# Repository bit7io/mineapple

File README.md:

# mineapple

A project to design an open source, modular mining system based around the ASICs reverse engineered by the [bitaxe](https://bitaxe.org/) project and [OSMU](https://www.opensourceminers.org/) community.

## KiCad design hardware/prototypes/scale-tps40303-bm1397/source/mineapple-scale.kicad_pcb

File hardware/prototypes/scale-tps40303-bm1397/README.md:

# Prototype BM1397 Scale
Known issues:
- M1 footprint incorrect
- R10 part number/footprint incorrect
- J1/J2 - TagConnect connector was used instead of SKEDD

Changes for V1.0:
- Fix known issues
- Move power monitoring to Core boards
- Remove 4V0 input
- Balance number of VPWR/PGND pins

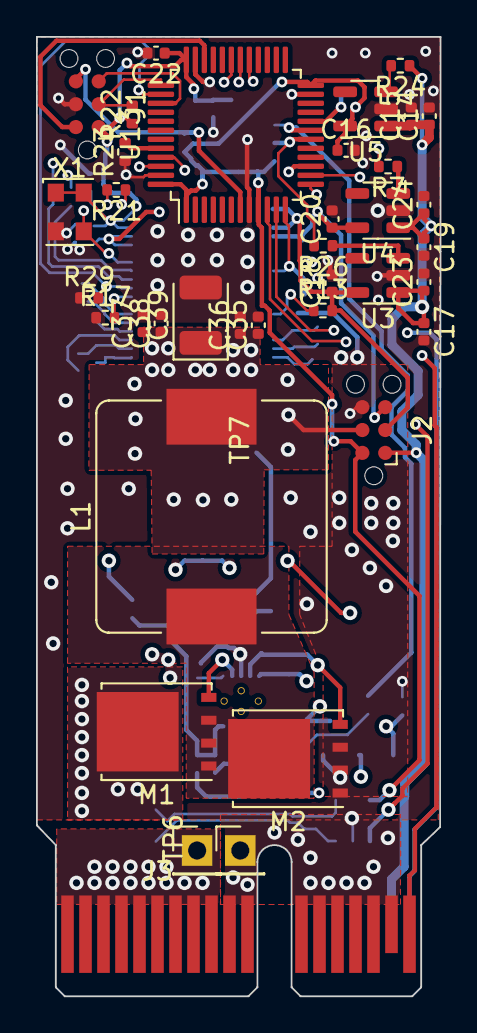
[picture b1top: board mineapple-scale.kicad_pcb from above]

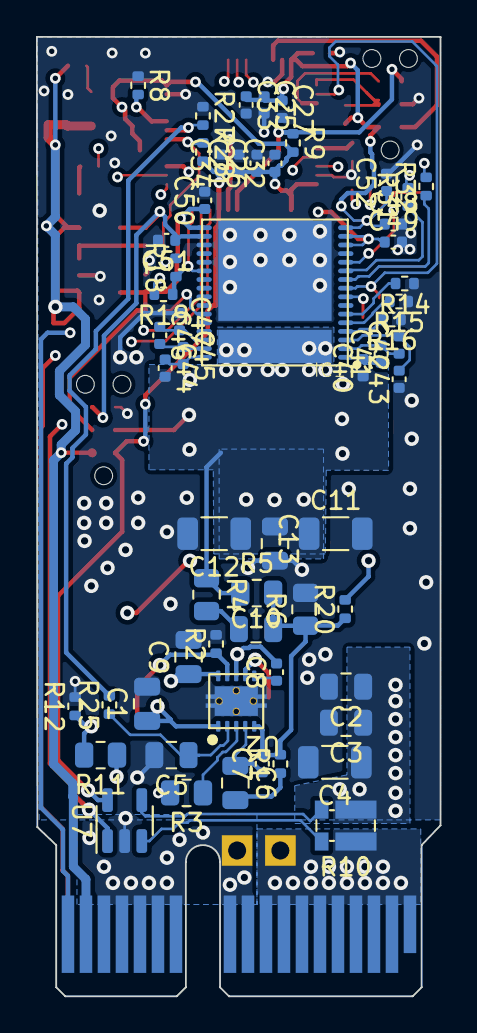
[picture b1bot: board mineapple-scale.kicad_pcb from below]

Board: 4 copper layers, 22.4 x 53.3 mm, 95 parts (58 on the bottom side), 58 nets.

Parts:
C1: 1uF; C_0805_2012Metric
C2, C3: 22uF; C_0805_2012Metric
C4: 47uF; C_1206_3216Metric
C5: 3.3nF; C_0805_2012Metric
C6: 11nF; C_0805_2012Metric
C7: 470pF; C_0402_1005Metric
C8, C22, C32, C33, C34: 100nF; C_0402_1005Metric
C9: 10uF; C_0805_2012Metric
C10: 3.9nF; C_0805_2012Metric
C11, C12: 220uF; C_1206_3216Metric
C13: 100uF; C_0805_2012Metric
C14, C16, C18, C20, C21, C23, C24, C27, C35, C37, C40, C41, C42, C43, C44, C45, C46, C47, C48, C49, C50, C51: 1uF; C_0402_1005Metric
C15, C17, C19, C36, C38, C52: 0.1uF; C_0402_1005Metric
C25: 10nF; C_0402_1005Metric
C26: 4.7uF; C_0402_1005Metric
C39: 330uF; CP_EIA-3528-21_Kemet-B
IC1: BM1397_mode1; BM1397
J1, J2: Conn_SKEDD_6pos; Tag-Connect_TC2030-IDC-NL_2x03_P1.27mm_Vertical
J3: MAS_Edge_Connector; BUS_PCIexpress_x1
L1: 1.3uH; L_Bourns_SRP1245A
M1: CSD17304Q3; TDSON-8-1
M2: CSD17573Q5B; TDSON-8-1
R1: 3.83k; R_0402_1005Metric
R2: 1.74k; R_0402_1005Metric
R3, R11: 100k; R_0805_2012Metric
R4: 432; R_0805_2012Metric
R5: 10k; R_0805_2012Metric
R6: 6.65k; R_0805_2012Metric
R7, R18, R20, R21, R25, R26, R31, R32: 1k; R_0402_1005Metric
R8, R9, R12, R13, R14, R15, R16, R17, R22, R23, R24, R27, R28, R29: 15k; R_0402_1005Metric
R10: 2mOhm; R_Shunt_Vishay_WSKW0612
R19: 2k; R_0402_1005Metric
TP6, TP7: TestPoint; PinHeader_1x01_P2.54mm_Vertical
U2: TPS40303DRCR; TPS40305
U3: MIC5504-1.8YM5; SOT-23-5
U4: TPS7A0508PDBV; SOT-23-5
U5: MIC5504-3.3YM5; SOT-23-5
U7: INA180A4; SOT-23-5
U13: STM32F072CBTx; LQFP-48_7x7mm_P0.5mm
X1: 25MHz; Oscillator_SMD_EuroQuartz_XO32-4Pin_3.2x2.5mm

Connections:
0V8: C20.1, C49.1, C51.1, IC1.14 (PLL_VDD), IC1.15 (VDDIO_08_0), IC1.18 (VDDIO_08_1), J2.5, U4.5 (OUT)
1V5: C11.1, C12.1, C13.1, C35.1, C36.1, C37.1, C38.1, C39.1, C40.1, C44.2, IC1.33 (VDD), J2.4, L1.2, R4.1, R5.1
1V8: C18.1, C22.1, C25.1, C27.1, C33.1, C48.1, C50.1, C52.1, IC1.16 (VDDIO_18_0), IC1.17 (VDDIO_18_1), J1.1, J2.3, R13.2, R22.1, U3.5 (VOUT), U13.36 (VDDIO2), X1.1 (EN), X1.4 (V+)
3V3: C16.1, C21.1, C26.1, C32.1, C34.1, J2.2, R9.2, R28.2, U5.5 (VOUT), U7.5 (V+), U13.1 (VBAT), U13.9 (VDDA), U13.24 (VDD), U13.48 (VDD)
4V0: C14.1, C15.1, C17.1, C19.1, C23.1, C24.1, J2.1, J3.A17 (4V0), R24.1, U3.1 (VIN), U4.1 (IN), U5.1 (VIN)
/MCU/SWDCLK: J1.3, R22.2, U13.37 (PA14)
/MCU/SWDIO: J1.2, U13.34 (PA13)
ADC12_IN0: U7.1, U13.10 (PA0)
ADC12_IN1: R11.2, R12.1, U13.11 (PA1)
CAN_RX: J3.A18 (CAN_RX), U13.45 (PB8)
CAN_TX: J3.B18 (CAN_TX), U13.46 (PB9)
EN0V8: R7.2, R8.2, U13.20 (PB2)
EN1V5: R25.2, R27.2, U13.19 (PB1)
EN1V8: R26.2, R28.1, U13.18 (PB0)
FB1V5: R20.2, U13.15 (PA5)
GND: C1.2, C2.2, C3.2, C4.2, C5.2, C9.2, C11.2, C12.2, C13.2, C14.2, C15.2, C16.2, C17.2, C18.2, C19.2, C20.2, C21.2, C22.2, C23.2, C24.2, C25.2, C26.2, C27.2, C32.2, C33.2, C34.2, C35.2, C36.2, C37.2, C38.2, C39.2, C43.1, C47.1, C48.2, C49.2, C50.2, C51.2, C52.2, IC1.13 (PLL_VSS), IC1.19 (VSS), IC1.21 (TEMP_N), IC1.34 (VSS_0), J1.4, J2.6, J3.A10 (PGND), J3.A11 (PGND), J3.A12 (PGND), J3.A13 (PGND), J3.A14 (PGND), J3.A15 (PGND), J3.A16 (PGND), J3.B10 (PGND), J3.B11 (PGND), J3.B12 (PGND), J3.B13 (PGND), J3.B14 (PGND), J3.B15 (PGND), J3.B16 (PGND), J3.B17 (PGND), M2.1 (S), M2.2 (S), M2.3 (S), R2.2, R6.2, R8.1, R12.2, R14.1, R15.1, R16.1, R17.1, R23.1, R27.1, R29.1, TP7.1, U2.11 (GND), U3.2 (GND), U4.2 (GND), U5.2 (GND), U7.2 (GND), U13.8 (VSSA), U13.23 (VSS), U13.35 (VSS), U13.47 (VSS), X1.2 (GND)
unnamed: C6.2, R1.1
unnamed: C10.1, R4.2
unnamed: IC1.4 (ADDR0), R16.2
unnamed: IC1.5 (ADDR1), R15.2
unnamed: IC1.6 (ADDR2), R14.2
unnamed: IC1.8 (BI), R17.2
unnamed: IC1.12 (CLKI), R21.2, X1.3 (OUT)
unnamed: IC1.27 (RI), R13.1
unnamed: C42.2, C43.2, IC1.3 (VDD1_0)
unnamed: C46.1, C47.2, IC1.30 (VDD1_1)
unnamed: C41.2, C42.1, IC1.2 (VDD2_0)
unnamed: C45.1, C46.2, IC1.31 (VDD2_1)
unnamed: C40.2, C41.1, IC1.1 (VDD3_0)
unnamed: C44.1, C45.2, IC1.32 (VDD3_1)
unnamed: C1.1, C2.1, C3.1, C4.1, M1.5 (D), R10.4, U2.1 (VDD)
unnamed: M1.4 (G), U2.7 (HDRV)
unnamed: C8.2, L1.1, M1.1 (S), M1.2 (S), M1.3 (S), M2.5 (D), U2.8 (SW)
unnamed: M2.4 (G), R2.1, U2.9 (LDRV/OC)
unnamed: C8.1, U2.6 (BOOT)
unnamed: C9.1, R3.2, U2.10 (BP)
unnamed: C6.1, C7.1, U2.4 (COMP)
unnamed: C5.1, R25.1, U2.2 (EN/SS)
unnamed: C7.2, C10.2, R1.2, R5.2, R6.1, R20.1, U2.5 (FB)
unnamed: R3.1, U2.3 (PGOOD)
unnamed: R26.1, U3.3 (EN)
unnamed: R7.1, U4.3 (EN)
unnamed: R24.2, U5.3 (EN)
unnamed: R10.2, U7.3 (+)
unnamed: R10.3, U7.4 (-)
unnamed: R23.2, U13.44 (BOOT0)
unnamed: R18.2, U13.13 (PA3)
unnamed: R19.2, U13.14 (PA4)
unnamed: R31.2, U13.30 (PA9)
unnamed: R32.2, U13.31 (PA10)
SWO: J1.5, U13.39 (PB3)
TEMP_P: IC1.22 (TEMP_P), R18.1, R19.1, U13.12 (PA2)
UCLK: R21.1, U13.29 (PA8)
URST: IC1.9 (NRSTI), R29.2, U13.38 (PA15)
URXD: IC1.10 (RO), R32.1
UTXD: IC1.11 (CI), R31.1
VPWR: J3.A1 (VPWR), J3.A2 (VPWR), J3.A3 (VPWR), J3.A4 (VPWR), J3.A5 (VPWR), J3.A6 (VPWR), J3.A7 (VPWR), J3.A8 (VPWR), J3.A9 (VPWR), J3.B1 (VPWR), J3.B2 (VPWR), J3.B3 (VPWR), J3.B4 (VPWR), J3.B5 (VPWR), J3.B6 (VPWR), J3.B7 (VPWR), J3.B8 (VPWR), J3.B9 (VPWR), R10.1, R11.1, TP6.1
nRESET: J1.6, R9.1, U13.7 (NRST)

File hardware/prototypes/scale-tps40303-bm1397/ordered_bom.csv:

Reference,Value,Footprint,Datasheet,DK,MPN,Qty,Qty10
C1,1uF,Capacitor_SMD:C_0805_2012Metric,~,1276-1029-1-ND,,1,10
"C2, C3",22uF,Capacitor_SMD:C_0805_2012Metric,~,1276-CL21A226MAYNNNECT-ND,,2,20
C4,47uF,Capacitor_SMD:C_1206_3216Metric,~,4713-GMC31X5R476M25NTCT-ND,,1,10
C5,3.3nF,Capacitor_SMD:C_0805_2012Metric,~,399-C0805C332K5RAC7800CT-ND,,1,10
C6,11nF,Capacitor_SMD:C_0805_2012Metric,~,490-8297-1-ND,,1,10
C7,470pF,Capacitor_SMD:C_0402_1005Metric,~,490-GCM155R71H471KA37JCT-ND,,1,10
"C8, C22, C32-C34",100nF,Capacitor_SMD:C_0402_1005Metric,~,1276-CL05B104KP5VPNCCT-ND,,5,50
C9,10uF,Capacitor_SMD:C_0805_2012Metric,~,1276-1096-1-ND,,1,10
C10,3.9nF,Capacitor_SMD:C_0805_2012Metric,~,478-KGM21NR71H392KTCT-ND,,1,10
"C11, C12",220uF,Capacitor_SMD:C_1206_3216Metric,~,718-2369-1-ND,,2,20
C13,100uF,Capacitor_SMD:C_0805_2012Metric,~,490-GRM21BR60G107ME11KCT-ND,,1,10
"C14, C16, C18, C20, C21, C23, C24, C27, C35, C37, C40-C51",1uF,Capacitor_SMD:C_0402_1005Metric,~,1276-1010-1-ND,,22,220
"C15, C17, C19, C36, C38, C52",0.1uF,Capacitor_SMD:C_0402_1005Metric,~,1276-1043-1-ND,,6,60
C25,10nF,Capacitor_SMD:C_0402_1005Metric,~,399-C0402C103K3REC7411CT-ND,,1,10
C26,4.7uF,Capacitor_SMD:C_0402_1005Metric,~,1276-1482-1-ND,,1,10
C39,330uF,Capacitor_Tantalum_SMD:CP_EIA-3528-21_Kemet-B,~,399-T490B337M004ATE800CT-ND,,1,10
IC1,BM1397_mode1,bitaxe:BM1397,,,,1,10
"J1, J2",Conn_SKEDD_6pos,Connector:Tag-Connect_TC2030-IDC-NL_2x03_P1.27mm_Vertical,4.90108E+11,,,2,20
J3,MAS_Edge_Connector,Connector_PCBEdge:BUS_PCIexpress_x1,,,,1,10
L1,1.3uH,Inductor_SMD:L_Bourns_SRP1245A,~,SRP1265A-1R8MCT-ND,SRP1265A-1R8M,1,10
M1,CSD17304Q3,Package_TO_SOT_SMD:TDSON-8-1,http://www.ti.com/lit/gpn/csd17304q3,296-27509-1-ND,,1,10
M2,CSD17573Q5B,Package_TO_SOT_SMD:TDSON-8-1,http://www.ti.com/lit/gpn/csd17573q5b,296-39836-1-ND,,1,10
R1,3.83k,Resistor_SMD:R_0402_1005Metric,~,311-3.83KLRCT-ND,,1,10
R2,1.74k,Resistor_SMD:R_0402_1005Metric,~,YAG3046CT-ND,,1,10
"R3, R11",100k,Resistor_SMD:R_0805_2012Metric,~,RMCF0805FT100KCT-ND,,2,20
R4,432,Resistor_SMD:R_0805_2012Metric,~,RMCF0805FT432RCT-ND,,1,10
R5,10k,Resistor_SMD:R_0805_2012Metric,~,RMCF0805FT10K0CT-ND,,1,10
R6,6.65k,Resistor_SMD:R_0805_2012Metric,~,RMCF0805FT6K65CT-ND,,1,10
"R7, R18, R20, R21, R25, R26, R31, R32",1k,Resistor_SMD:R_0402_1005Metric,~,311-1.00KLRCT-ND,,8,80
"R8, R9, R12-R17, R22-R24, R27-R29",15k,Resistor_SMD:R_0402_1005Metric,~,P15.0KLCT-ND,,14,140
R10,2mOhm,Resistor_SMD:R_Shunt_Vishay_WSKW0612,~,4463-D1MPC1206DR003FF-T5CT-ND,,1,10
R19,2k,Resistor_SMD:R_0402_1005Metric,~,P2.00KLCT-ND,,1,10
"TP6, TP7",TestPoint,Connector_PinHeader_2.54mm:PinHeader_1x01_P2.54mm_Vertical,~,,,2,20
U2,TPS40303DRCR,mineapple:TPS40305,TPS40303DRCR,296-37444-1-ND,,1,10
U3,MIC5504-1.8YM5,Package_TO_SOT_SMD:SOT-23-5,http://ww1.microchip.com/downloads/en/DeviceDoc/MIC550X.pdf,576-4879-1-ND,,1,10
U4,TPS7A0508PDBV,Package_TO_SOT_SMD:SOT-23-5,https://www.ti.com/lit/ds/symlink/tps7a05.pdf,296-TPS7A0508PDBVRCT-ND,,1,10
U5,MIC5504-3.3YM5,Package_TO_SOT_SMD:SOT-23-5,http://ww1.microchip.com/downloads/en/DeviceDoc/MIC550X.pdf,576-4764-1-ND,,1,10
U7,INA180A4,Package_TO_SOT_SMD:SOT-23-5,http://www.ti.com/lit/ds/symlink/ina180.pdf,296-47655-1-ND,,1,10
U13,STM32F072CBTx,Package_QFP:LQFP-48_7x7mm_P0.5mm,https://www.st.com/resource/en/datasheet/stm32f072cb.pdf,497-18747-1-ND,,1,10
X1,25MHz,Oscillator:Oscillator_SMD_EuroQuartz_XO32-4Pin_3.2x2.5mm,http://cdn-reichelt.de/documents/datenblatt/B400/XO32.pdf,1908-O250-JO32-B-1V3-1-T1-LFCT-ND,,1,10
